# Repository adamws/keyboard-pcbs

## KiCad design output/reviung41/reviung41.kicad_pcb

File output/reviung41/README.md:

## reviung41/reviung41

[layout](reviung41-kle.json) - [PCB](reviung41.kicad_pcb)

{:loading="lazy"}

[Open in keyboard-layout-editor](http://www.keyboard-layout-editor.com/##@@_x:3;&=0,3&_x:5;&=3,2;&@_x:2&y:-0.85;&=0,2&_x:1;&=0,4&_x:3;&=3,1&_x:1;&=3,3;&@_x:1&y:-0.8;&=0,1&_x:3;&=0,5&_x:1;&=3,0&_x:3;&=3,4;&@_y:-0.85&c=#777777;&=0,0&_x:11;&=3,5;&@_x:3&y:-0.5&c=#cccccc;&=1,3&_x:5;&=4,2;&@_x:2&y:-0.85;&=1,2&_x:1;&=1,4&_x:3;&=4,1&_x:1;&=4,3;&@_x:1&y:-0.8;&=1,1&_x:3;&=1,5&_x:1;&=4,0&_x:3;&=4,4;&@_y:-0.85&c=#aaaaaa;&=1,0&_x:11;&=4,5;&@_x:3&y:-0.5&c=#cccccc;&=2,3&_x:5;&=5,2;&@_x:2&y:-0.85;&=2,2&_x:1;&=2,4&_x:3;&=5,1&_x:1;&=5,3;&@_x:1&y:-0.8;&=2,1&_x:3;&=2,5&_x:1;&=5,0&_x:3;&=5,4;&@_y:-0.85&c=#aaaaaa;&=2,0&_x:11;&=5,5;&@_x:3&w:1.25;&=6,0&_w:1.25;&=6,1&_w:2;&=6,2&_w:1.25;&=6,3&_w:1.25;&=6,4)

{:loading="lazy"}

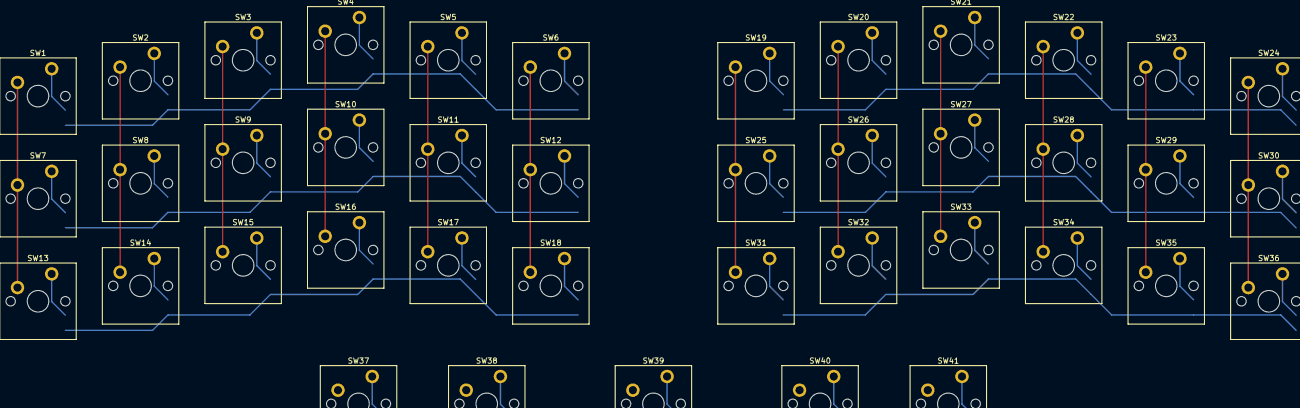
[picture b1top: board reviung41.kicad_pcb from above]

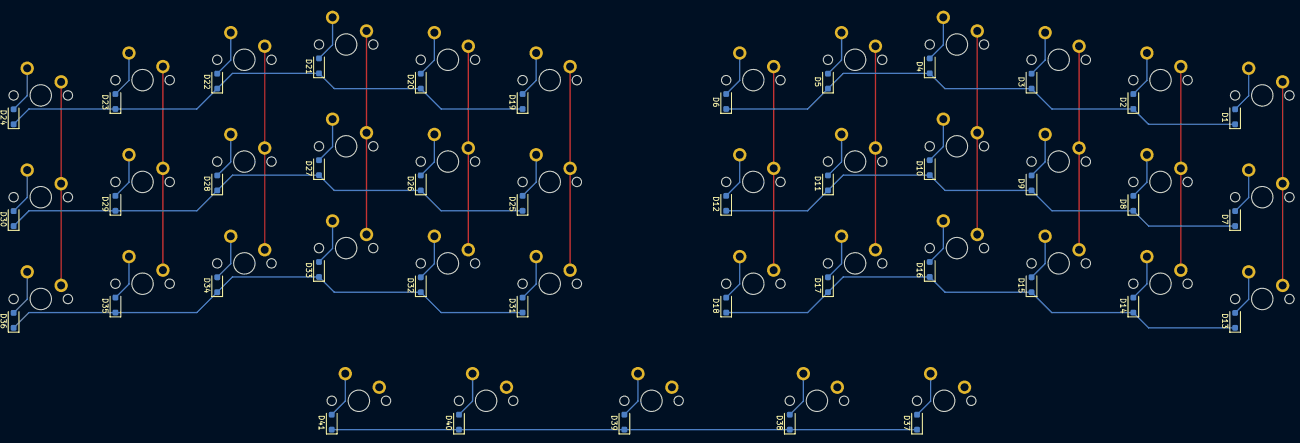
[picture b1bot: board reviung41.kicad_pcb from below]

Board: 2 copper layers, 82 parts (41 on the bottom side), 54 nets.

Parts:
D1, D2, D3, D4, D5, D6, D7, D8, D9, D10, D11, D12, D13, D14, D15, D16, D17, D18, D19, D20, D21, D22, D23, D24, D25, D26, D27, D28, D29, D30, D31, D32, D33, D34, D35, D36, D37, D38, D39, D40, D41: D_SOD-123F
SW1, SW2, SW3, SW4, SW5, SW6, SW7, SW8, SW9, SW10, SW11, SW12, SW13, SW14, SW15, SW16, SW17, SW18, SW19, SW20, SW21, SW22, SW23, SW24, SW25, SW26, SW27, SW28, SW29, SW30, SW31, SW32, SW33, SW34, SW35, SW36, SW37, SW38, SW39, SW40, SW41: SW_Cherry_MX_PCB_1.00u

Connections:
COL0: SW1.1, SW7.1, SW13.1, SW19.1, SW25.1, SW31.1, SW37.1
COL1: SW2.1, SW8.1, SW14.1, SW20.1, SW26.1, SW32.1, SW38.1
COL2: SW3.1, SW9.1, SW15.1, SW21.1, SW27.1, SW33.1, SW39.1
COL3: SW4.1, SW10.1, SW16.1, SW22.1, SW28.1, SW34.1, SW40.1
COL4: SW5.1, SW11.1, SW17.1, SW23.1, SW29.1, SW35.1, SW41.1
COL5: SW6.1, SW12.1, SW18.1, SW24.1, SW30.1, SW36.1
unnamed: D1.2, SW1.2
unnamed: D2.2, SW2.2
unnamed: D3.2, SW3.2
unnamed: D4.2, SW4.2
unnamed: D5.2, SW5.2
unnamed: D6.2, SW6.2
unnamed: D7.2, SW7.2
unnamed: D8.2, SW8.2
unnamed: D9.2, SW9.2
unnamed: D10.2, SW10.2
unnamed: D11.2, SW11.2
unnamed: D12.2, SW12.2
unnamed: D13.2, SW13.2
unnamed: D14.2, SW14.2
unnamed: D15.2, SW15.2
unnamed: D16.2, SW16.2
unnamed: D17.2, SW17.2
unnamed: D18.2, SW18.2
unnamed: D19.2, SW19.2
unnamed: D20.2, SW20.2
unnamed: D21.2, SW21.2
unnamed: D22.2, SW22.2
unnamed: D23.2, SW23.2
unnamed: D24.2, SW24.2
unnamed: D25.2, SW25.2
unnamed: D26.2, SW26.2
unnamed: D27.2, SW27.2
unnamed: D28.2, SW28.2
unnamed: D29.2, SW29.2
unnamed: D30.2, SW30.2
unnamed: D31.2, SW31.2
unnamed: D32.2, SW32.2
unnamed: D33.2, SW33.2
unnamed: D34.2, SW34.2
unnamed: D35.2, SW35.2
unnamed: D36.2, SW36.2
unnamed: D37.2, SW37.2
unnamed: D38.2, SW38.2
unnamed: D39.2, SW39.2
unnamed: D40.2, SW40.2
unnamed: D41.2, SW41.2
ROW0: D1.1, D2.1, D3.1, D4.1, D5.1, D6.1
ROW1: D7.1, D8.1, D9.1, D10.1, D11.1, D12.1
ROW2: D13.1, D14.1, D15.1, D16.1, D17.1, D18.1
ROW3: D19.1, D20.1, D21.1, D22.1, D23.1, D24.1
ROW4: D25.1, D26.1, D27.1, D28.1, D29.1, D30.1
ROW5: D31.1, D32.1, D33.1, D34.1, D35.1, D36.1
ROW6: D37.1, D38.1, D39.1, D40.1, D41.1

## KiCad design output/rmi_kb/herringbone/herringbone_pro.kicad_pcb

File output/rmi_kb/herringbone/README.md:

## rmi_kb/herringbone

[layout](herringbone-kle.json) - [PCB](herringbone.kicad_pcb)

{:loading="lazy"}

[Open in keyboard-layout-editor](http://www.keyboard-layout-editor.com/##@@_x:2.5&c=#777777;&=0,0&_x:0.25&c=#aaaaaa;&=0,1&=0,2&=0,3&=0,4&_x:0.25&c=#777777;&=0,5&=0,6&=0,7&=0,8&_x:0.25&c=#aaaaaa;&=0,9&=0,10&=0,11&=0,12&_x:0.25;&=0,13&_x:0.5&c=#777777;&=0,14;&@_x:2.5&y:0.25&c=#cccccc;&=1,0&=1,1&=1,2&=1,3&=1,4&=1,5&=1,6&=1,7&=1,8&=1,9&=1,10&=1,11&=1,12&_c=#aaaaaa&w:2;&=1,13%0A%0A%0A0,0&_x:0.5;&=1,14;&@_x:2.5&w:1.5;&=2,0&_c=#cccccc;&=2,1&=2,2&=2,3&=2,4&=2,5&=2,6&=2,7&=2,8&=2,9&=2,10&=2,11&=2,12&_w:1.5;&=2,13%0A%0A%0A1,0&_x:0.5&c=#aaaaaa;&=2,14;&@_x:2.5&w:1.75;&=3,0&_c=#cccccc;&=3,1&=3,2&=3,3&=3,4&=3,5&=3,6&=3,7&=3,8&=3,9&=3,10&=3,11&_c=#777777&w:2.25;&=3,13%0A%0A%0A1,0&_x:0.5&c=#aaaaaa;&=3,14;&@_x:2.5&w:2.25;&=4,0%0A%0A%0A2,0&_c=#cccccc;&=4,1&=4,2&=4,3&=4,4&=4,5&=4,6&=4,7&=4,8&=4,9&=4,10&_c=#aaaaaa&w:1.75;&=4,11&_x:1.5;&=4,14;&@_x:16.75&y:-0.75&c=#777777;&=4,13;&@_x:2.5&y:-0.25&c=#aaaaaa&w:1.25;&=5,0%0A%0A%0A3,0&_w:1.25;&=5,2%0A%0A%0A3,0&_w:1.25;&=5,3%0A%0A%0A3,0&_c=#cccccc&w:6.25;&=5,5%0A%0A%0A3,0&_c=#aaaaaa&w:1.5;&=5,9%0A%0A%0A3,0&_w:1.5;&=5,10%0A%0A%0A3,0;&@_x:15.75&y:-0.75&c=#777777;&=5,12&=5,13&=5,14;&@_x:19.5&y:-5.25&c=#aaaaaa;&=1,13%0A%0A%0A0,1&=3,12%0A%0A%0A0,1;&@_x:20.25&c=#777777&w:1.25&h:2&w2:1.5&h2:1&x2:-0.25;&=2,13%0A%0A%0A1,1;&@_x:19.25&c=#cccccc;&=3,13%0A%0A%0A1,1;&@_c=#aaaaaa&w:1.25;&=4,0%0A%0A%0A2,1&_c=#cccccc;&=5,1%0A%0A%0A2,1;&@_x:2.5&y:1.25&c=#aaaaaa&w:1.5;&=5,0%0A%0A%0A3,1&_w:1.5;&=5,3%0A%0A%0A3,1&_c=#cccccc&w:7;&=5,5%0A%0A%0A3,1&_c=#aaaaaa&w:1.5;&=5,9%0A%0A%0A3,1&_w:1.5;&=5,10%0A%0A%0A3,1)

{:loading="lazy"}

## rmi_kb/herringbone/herringbone_pro

[layout](herringbone_pro-kle.json) - [PCB](herringbone_pro.kicad_pcb)

{:loading="lazy"}

[Open in keyboard-layout-editor](http://www.keyboard-layout-editor.com/##@@_x:2.5&c=#777777;&=0,0&_x:0.25&c=#aaaaaa;&=0,1&=0,2&=0,3&=0,4&_x:0.25&c=#777777;&=0,5&=0,6&=0,7&=0,8&_x:0.25&c=#aaaaaa;&=0,9&=0,10&=0,11&=0,12&_x:0.25;&=0,13&_x:0.5&c=#cccccc;&=6,0&_c=#777777;&=0,14&_c=#cccccc;&=6,1;&@_x:2.5&y:0.25;&=1,0&=1,1&=1,2&=1,3&=1,4&=1,5&=1,6&=1,7&=1,8&=1,9&=1,10&=1,11&=1,12&_c=#aaaaaa&w:2;&=1,13%0A%0A%0A0,0&_x:0.5;&=1,14;&@_x:2.5&w:1.5;&=2,0&_c=#cccccc;&=2,1&=2,2&=2,3&=2,4&=2,5&=2,6&=2,7&=2,8&=2,9&=2,10&=2,11&=2,12&_w:1.5;&=2,13%0A%0A%0A1,0&_x:0.5&c=#aaaaaa;&=2,14;&@_x:2.5&w:1.75;&=3,0&_c=#cccccc;&=3,1&=3,2&=3,3&=3,4&=3,5&=3,6&=3,7&=3,8&=3,9&=3,10&=3,11&_c=#777777&w:2.25;&=3,13%0A%0A%0A1,0&_x:0.5&c=#aaaaaa;&=3,14;&@_x:2.5&w:2.25;&=4,0%0A%0A%0A2,0&_c=#cccccc;&=4,1&=4,2&=4,3&=4,4&=4,5&=4,6&=4,7&=4,8&=4,9&=4,10&_c=#aaaaaa&w:1.75;&=4,11&_x:1.5;&=4,14;&@_x:16.75&y:-0.75&c=#777777;&=4,13;&@_x:2.5&y:-0.25&c=#aaaaaa&w:1.25;&=5,0%0A%0A%0A3,0&_w:1.25;&=5,2%0A%0A%0A3,0&_w:1.25;&=5,3%0A%0A%0A3,0&_c=#cccccc&w:6.25;&=5,5%0A%0A%0A3,0&_c=#aaaaaa&w:1.5;&=5,9%0A%0A%0A3,0&_w:1.5;&=5,10%0A%0A%0A3,0;&@_x:15.75&y:-0.75&c=#777777;&=5,12&=5,13&=5,14;&@_x:19.5&y:-5.25&c=#aaaaaa;&=1,13%0A%0A%0A0,1&=3,12%0A%0A%0A0,1;&@_x:20.25&c=#777777&w:1.25&h:2&w2:1.5&h2:1&x2:-0.25;&=2,13%0A%0A%0A1,1;&@_x:19.25&c=#cccccc;&=3,13%0A%0A%0A1,1;&@_c=#aaaaaa&w:1.25;&=4,0%0A%0A%0A2,1&_c=#cccccc;&=5,1%0A%0A%0A2,1;&@_x:2.5&y:1.25&c=#aaaaaa&w:1.5;&=5,0%0A%0A%0A3,1&_w:1.5;&=5,3%0A%0A%0A3,1&_c=#cccccc&w:7;&=5,5%0A%0A%0A3,1&_c=#aaaaaa&w:1.5;&=5,9%0A%0A%0A3,1&_w:1.5;&=5,10%0A%0A%0A3,1;&@_x:2.5&w:1.25;&=5,0%0A%0A%0A3,2&_w:1.25;&=5,2%0A%0A%0A3,2&_w:1.25;&=5,3%0A%0A%0A3,2&_c=#cccccc&w:2.25;&=5,4%0A%0A%0A3,2&=5,5%0A%0A%0A3,2&_w:3;&=5,7%0A%0A%0A3,2&_c=#aaaaaa&w:1.5;&=5,9%0A%0A%0A3,2&_w:1.5;&=5,10%0A%0A%0A3,2)

{:loading="lazy"}

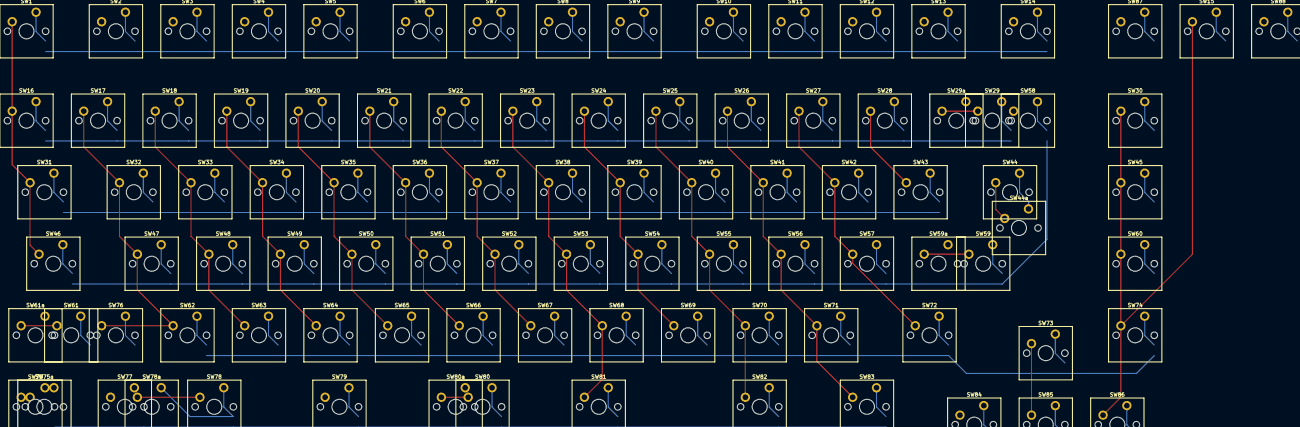
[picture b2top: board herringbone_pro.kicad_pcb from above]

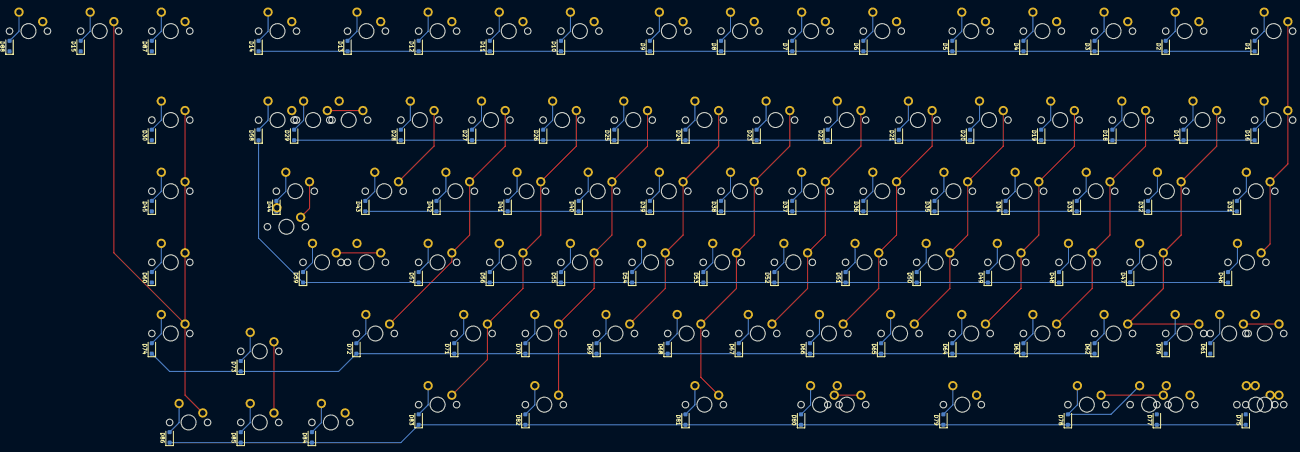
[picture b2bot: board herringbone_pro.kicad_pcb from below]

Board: 2 copper layers, 183 parts (88 on the bottom side), 110 nets.

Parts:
D1, D2, D3, D4, D5, D6, D7, D8, D9, D10, D11, D12, D13, D14, D15, D16, D17, D18, D19, D20, D21, D22, D23, D24, D25, D26, D27, D28, D29, D30, D31, D32, D33, D34, D35, D36, D37, D38, D39, D40, D41, D42, D43, D44, D45, D46, D47, D48, D49, D50, D51, D52, D53, D54, D55, D56, D57, D58, D59, D60, D61, D62, D63, D64, D65, D66, D67, D68, D69, D70, D71, D72, D73, D74, D75, D76, D77, D78, D79, D80, D81, D82, D83, D84, D85, D86, D87, D88: D_SOD-123F
SW1, SW2, SW3, SW4, SW5, SW6, SW7, SW8, SW9, SW10, SW11, SW12, SW13, SW14, SW15, SW16, SW17, SW18, SW19, SW20, SW21, SW22, SW23, SW24, SW25, SW26, SW27, SW28, SW29, SW29a, SW30, SW31, SW32, SW33, SW34, SW35, SW36, SW37, SW38, SW39, SW40, SW41, SW42, SW43, SW44, SW44a, SW45, SW46, SW47, SW48, SW49, SW50, SW51, SW52, SW53, SW54, SW55, SW56, SW57, SW58, SW59, SW59a, SW60, SW61, SW61a, SW62, SW63, SW64, SW65, SW66, SW67, SW68, SW69, SW70, SW71, SW72, SW73, SW74, SW75, SW75a, SW76, SW77, SW78, SW78a, SW79, SW80, SW80a, SW81, SW82, SW83, SW84, SW85, SW86, SW87, SW88: SW_Cherry_MX_PCB_1.00u

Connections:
COL0: SW1.1, SW16.1, SW31.1, SW46.1, SW61.1, SW61a.1, SW75.1, SW75a.1, SW87.1
COL1: SW2.1, SW17.1, SW32.1, SW47.1, SW62.1, SW76.1, SW88.1
COL2: SW3.1, SW18.1, SW33.1, SW48.1, SW63.1, SW77.1
COL3: SW4.1, SW19.1, SW34.1, SW49.1, SW64.1, SW78.1, SW78a.1
COL4: SW5.1, SW20.1, SW35.1, SW50.1, SW65.1, SW79.1
COL5: SW6.1, SW21.1, SW36.1, SW51.1, SW66.1, SW80.1, SW80a.1
COL6: SW7.1, SW22.1, SW37.1, SW52.1, SW67.1
COL7: SW8.1, SW23.1, SW38.1, SW53.1, SW68.1, SW81.1
COL8: SW9.1, SW24.1, SW39.1, SW54.1, SW69.1
COL9: SW10.1, SW25.1, SW40.1, SW55.1, SW70.1, SW82.1
COL10: SW11.1, SW26.1, SW41.1, SW56.1, SW71.1, SW83.1
COL11: SW12.1, SW27.1, SW42.1, SW57.1, SW72.1
COL12: SW13.1, SW28.1, SW43.1, SW58.1, SW84.1
COL13: SW14.1, SW29.1, SW29a.1, SW44.1, SW44a.1, SW59.1, SW59a.1, SW73.1, SW85.1
COL14: SW15.1, SW30.1, SW45.1, SW60.1, SW74.1, SW86.1
unnamed: D1.2, SW1.2
unnamed: D2.2, SW2.2
unnamed: D3.2, SW3.2
unnamed: D4.2, SW4.2
unnamed: D5.2, SW5.2
unnamed: D6.2, SW6.2
unnamed: D7.2, SW7.2
unnamed: D8.2, SW8.2
unnamed: D9.2, SW9.2
unnamed: D10.2, SW10.2
unnamed: D11.2, SW11.2
unnamed: D12.2, SW12.2
unnamed: D13.2, SW13.2
unnamed: D14.2, SW14.2
unnamed: D15.2, SW15.2
unnamed: D16.2, SW16.2
unnamed: D17.2, SW17.2
unnamed: D18.2, SW18.2
unnamed: D19.2, SW19.2
unnamed: D20.2, SW20.2
unnamed: D21.2, SW21.2
unnamed: D22.2, SW22.2
unnamed: D23.2, SW23.2
unnamed: D24.2, SW24.2
unnamed: D25.2, SW25.2
unnamed: D26.2, SW26.2
unnamed: D27.2, SW27.2
unnamed: D28.2, SW28.2
unnamed: D29.2, SW29.2, SW29a.2
unnamed: D30.2, SW30.2
unnamed: D31.2, SW31.2
unnamed: D32.2, SW32.2
unnamed: D33.2, SW33.2
unnamed: D34.2, SW34.2
unnamed: D35.2, SW35.2
unnamed: D36.2, SW36.2
unnamed: D37.2, SW37.2
unnamed: D38.2, SW38.2
unnamed: D39.2, SW39.2
unnamed: D40.2, SW40.2
unnamed: D41.2, SW41.2
unnamed: D42.2, SW42.2
unnamed: D43.2, SW43.2
unnamed: D44.2, SW44.2, SW44a.2
unnamed: D45.2, SW45.2
unnamed: D46.2, SW46.2
unnamed: D47.2, SW47.2
unnamed: D48.2, SW48.2
unnamed: D49.2, SW49.2
unnamed: D50.2, SW50.2
unnamed: D51.2, SW51.2
unnamed: D52.2, SW52.2
unnamed: D53.2, SW53.2
unnamed: D54.2, SW54.2
unnamed: D55.2, SW55.2
unnamed: D56.2, SW56.2
unnamed: D57.2, SW57.2
unnamed: D58.2, SW58.2
unnamed: D59.2, SW59.2, SW59a.2
unnamed: D60.2, SW60.2
unnamed: D61.2, SW61.2, SW61a.2
unnamed: D62.2, SW62.2
unnamed: D63.2, SW63.2
unnamed: D64.2, SW64.2
unnamed: D65.2, SW65.2
unnamed: D66.2, SW66.2
unnamed: D67.2, SW67.2
unnamed: D68.2, SW68.2
unnamed: D69.2, SW69.2
unnamed: D70.2, SW70.2
unnamed: D71.2, SW71.2
unnamed: D72.2, SW72.2
unnamed: D73.2, SW73.2
unnamed: D74.2, SW74.2
unnamed: D75.2, SW75.2, SW75a.2
unnamed: D76.2, SW76.2
unnamed: D77.2, SW77.2
unnamed: D78.2, SW78.2, SW78a.2
unnamed: D79.2, SW79.2
unnamed: D80.2, SW80.2, SW80a.2
unnamed: D81.2, SW81.2
unnamed: D82.2, SW82.2
unnamed: D83.2, SW83.2
unnamed: D84.2, SW84.2
unnamed: D85.2, SW85.2
unnamed: D86.2, SW86.2
unnamed: D87.2, SW87.2
unnamed: D88.2, SW88.2
ROW0: D1.1, D2.1, D3.1, D4.1, D5.1, D6.1, D7.1, D8.1, D9.1, D10.1, D11.1, D12.1, D13.1, D14.1, D15.1
ROW1: D16.1, D17.1, D18.1, D19.1, D20.1, D21.1, D22.1, D23.1, D24.1, D25.1, D26.1, D27.1, D28.1, D29.1, D30.1
ROW2: D31.1, D32.1, D33.1, D34.1, D35.1, D36.1, D37.1, D38.1, D39.1, D40.1, D41.1, D42.1, D43.1, D44.1, D45.1
ROW3: D46.1, D47.1, D48.1, D49.1, D50.1, D51.1, D52.1, D53.1, D54.1, D55.1, D56.1, D57.1, D58.1, D59.1, D60.1
ROW4: D61.1, D62.1, D63.1, D64.1, D65.1, D66.1, D67.1, D68.1, D69.1, D70.1, D71.1, D72.1, D73.1, D74.1
ROW5: D75.1, D76.1, D77.1, D78.1, D79.1, D80.1, D81.1, D82.1, D83.1, D84.1, D85.1, D86.1
ROW6: D87.1, D88.1
